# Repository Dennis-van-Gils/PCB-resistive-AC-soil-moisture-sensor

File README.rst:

.. image:: https://knowledge.autodesk.com/sites/default/files/product-logo-sm/eagle-2017-badge-75x75.png
    :target: https://www.autodesk.com/products/eagle/free-download
.. image:: https://img.shields.io/badge/License-MIT-purple.svg
    :target: https://github.com/Dennis-van-Gils/PCB-resistive-AC-soil-moisture-sensor/blob/master/LICENSE.txt

Resistive AC soil moisture sensor
=================================

This project involves a printed circuit board design to measure the resistance
between two metallic probes that can be placed inside soil as a measure of the
soil humidity. It uses AC current to sense the resistance between the probes,
preventing corrosion of the probes which otherwise would happen when a DC
current is used instead. The design is based on the
`SMX sensor <https://www.emesystems.com/smx/main.html>`__ by EME Systems.

The sensor can be supplied with either 3.3 V or 5.0 V and utilizes an onboard
3.0 V regulator powering a TLC555 timer. The output is a pulse train with an
amplitude equal to the supply voltage and of a variable frequency that
correlates to the measured resistance. The pulses are at a 50% duty cycle.

Contains EAGLE, Fusion360 and LTSpice project files.

- Github: https://github.com/Dennis-van-Gils/PCB-resistive-AC-soil-moisture-sensor

PCB design
==========

The PCB production Gerber files can be found `here. <EAGLE/AC_soil_sensor_v1.0_2022-05-01.zip>`__

.. image:: Fusion360/AC_soil_sensor_v1.0.png

.. image:: EAGLE/AC_soil_sensor_v1.0_schematic.png

Bill of materials
=================

+-----+-------------------+--------------------------------------+------------------------------------+
| IC1 | CMOS low-dropout voltage regulator, 3.0V 250mA           | MCP1700-3002E/TO                   |
+-----+-------------------+--------------------------------------+------------------------------------+
| IC2 | CMOS 555 timer, input 2V-15V                             | TLC555CP                           |
+-----+-------------------+--------------------------------------+------------------------------------+
| R1  | 4.7 kΩ  1/4W   5% | Resistor, carbon film                |                                    |
+-----+-------------------+--------------------------------------+------------------------------------+
| R2  | 100  Ω  1/4W   5% | Resistor, carbon film                |                                    |
+-----+-------------------+--------------------------------------+------------------------------------+
| R3  | 150 kΩ  1/4W   5% | Resistor, carbon film                |                                    |
+-----+-------------------+--------------------------------------+------------------------------------+
| R4  | 390  Ω  1/4W   5% | Resistor, carbon film                |                                    |
+-----+-------------------+--------------------------------------+------------------------------------+
| C1  | 1   μF   50V  10% | Capacitor, ceramic                   | KEMET C320C105K5N5TA91707301       |
+-----+-------------------+--------------------------------------+------------------------------------+
| C2  | 0.1 μF   50V  10% | Capacitor, ceramic                   | KEMET C320C104K5R5TA7301           |
+-----+-------------------+--------------------------------------+------------------------------------+
| C3  | 1   μF   50V      | Capacitor, aluminium electrolytic    |                                    |
+-----+-------------------+--------------------------------------+------------------------------------+
| C4  | 0.1 μF   63V   5% | Capacitor, metallized polyester film | TDK B32529C0104J                   |
+-----+-------------------+--------------------------------------+------------------------------------+
| C5  | 4.7 μF   25V  10% | Capacitor, ceramic                   | KEMET C320C475K3N5TA91707301       |
+-----+-------------------+--------------------------------------+------------------------------------+
| C6  | 4.7 μF   25V  10% | Capacitor, ceramic                   | KEMET C320C475K3N5TA91707301       |
+-----+-------------------+--------------------------------------+------------------------------------+

LTspice simulation
==================

The frequency-resistance relationship of the simulated idealized circuit:

.. image:: LTspice_simulation/SMX_simulation_v3_frequency_response.png

Dennis van Gils, 2022

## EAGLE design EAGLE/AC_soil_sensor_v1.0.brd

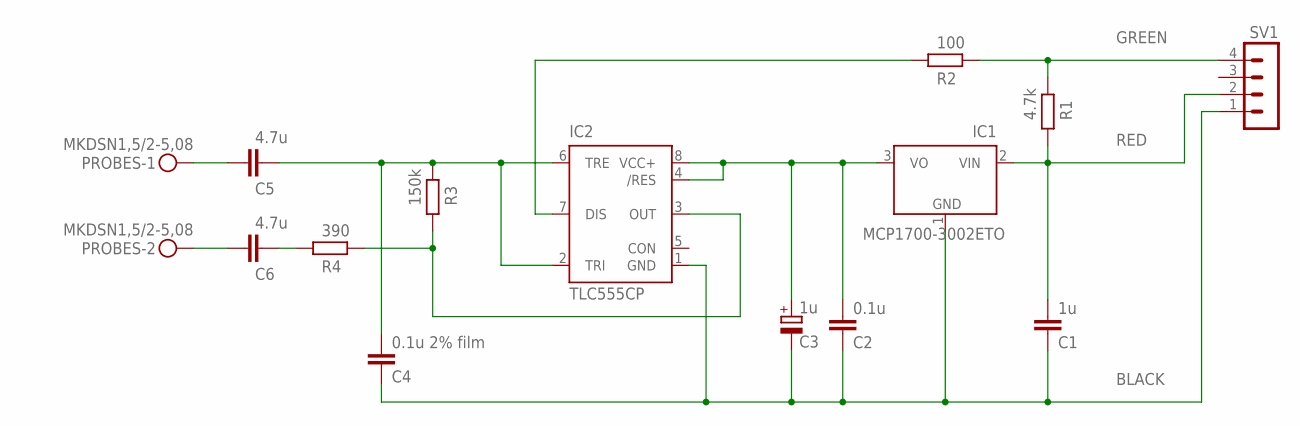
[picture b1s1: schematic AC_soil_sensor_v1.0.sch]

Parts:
C1: 1u; C025-025X050
C2: 0.1u; C050-025X075
C3: 1u; E2-5
C4: 0.1u 2% film; C050-025X075
C5, C6: 4.7u; C025-025X050
IC1: MCP1700-3002ETO; TO92
IC2: TLC555CP; DIL-08
PROBES: MKDSN1,5/2-5,08
R1: 4.7k; 0207/10
R2: 100; 0207/10
R3: 150k; 0207/10
R4: 390; 0207/10
SV1: MA04-1

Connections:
BLACK: C1.1, C2.2, C3.-, C4.2, IC1.1 (GND), IC2.1 (GND), SV1.1
GREEN: R1.2, R2.1, SV1.4
unnamed: C4.1, C5.2, IC2.2 (TRI), IC2.6 (TRE), R3.2
unnamed: C6.2, R4.1
unnamed: C5.1, PROBES.1
unnamed: C2.1, C3.+, IC1.3 (VO), IC2.4 (/RES), IC2.8 (VCC+)
unnamed: IC2.3 (OUT), R3.1, R4.2
unnamed: IC2.7 (DIS), R2.2
unnamed: C6.1, PROBES.2
RED: C1.2, IC1.2 (VIN), R1.1, SV1.2

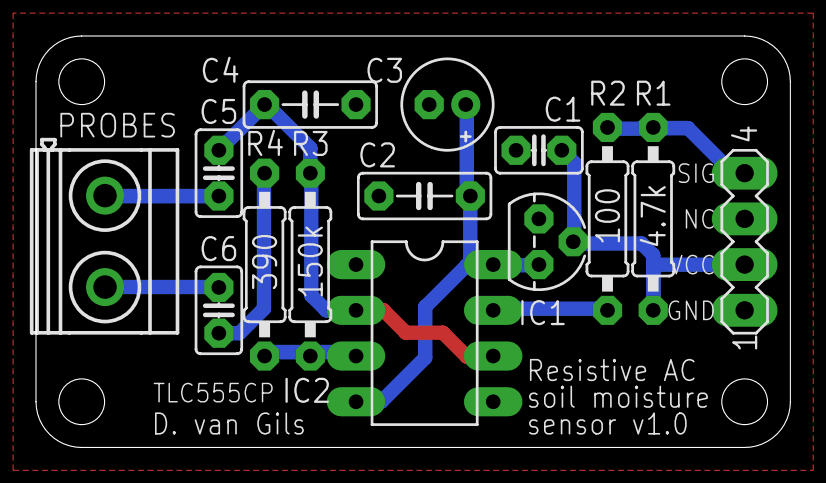
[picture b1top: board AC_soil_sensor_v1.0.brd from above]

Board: 2 copper layers, 41.9 x 22.9 mm, 14 parts (0 on the bottom side), 10 nets.

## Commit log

2022-05-01 Documentation
2022-05-01 Deleted
2022-05-13 Reorganize folders
2022-05-13 Arduino demo
2022-05-14 Proof of principle
2022-05-14 Streamline code
2022-05-14 Finalized minimum working example
2022-05-14 Captured into function
2022-05-14 Added itsybitsy32u4_5V
2022-05-18 Frequency to resistance best-fit transformation
2022-05-19 Move frequency calculation to outside of ISR
2022-05-19 Updated to better fitting parameters
2022-05-19 Added calibration results
2022-05-26 Made `frequency` a double instead of uint16_t
2022-05-26 In progress
